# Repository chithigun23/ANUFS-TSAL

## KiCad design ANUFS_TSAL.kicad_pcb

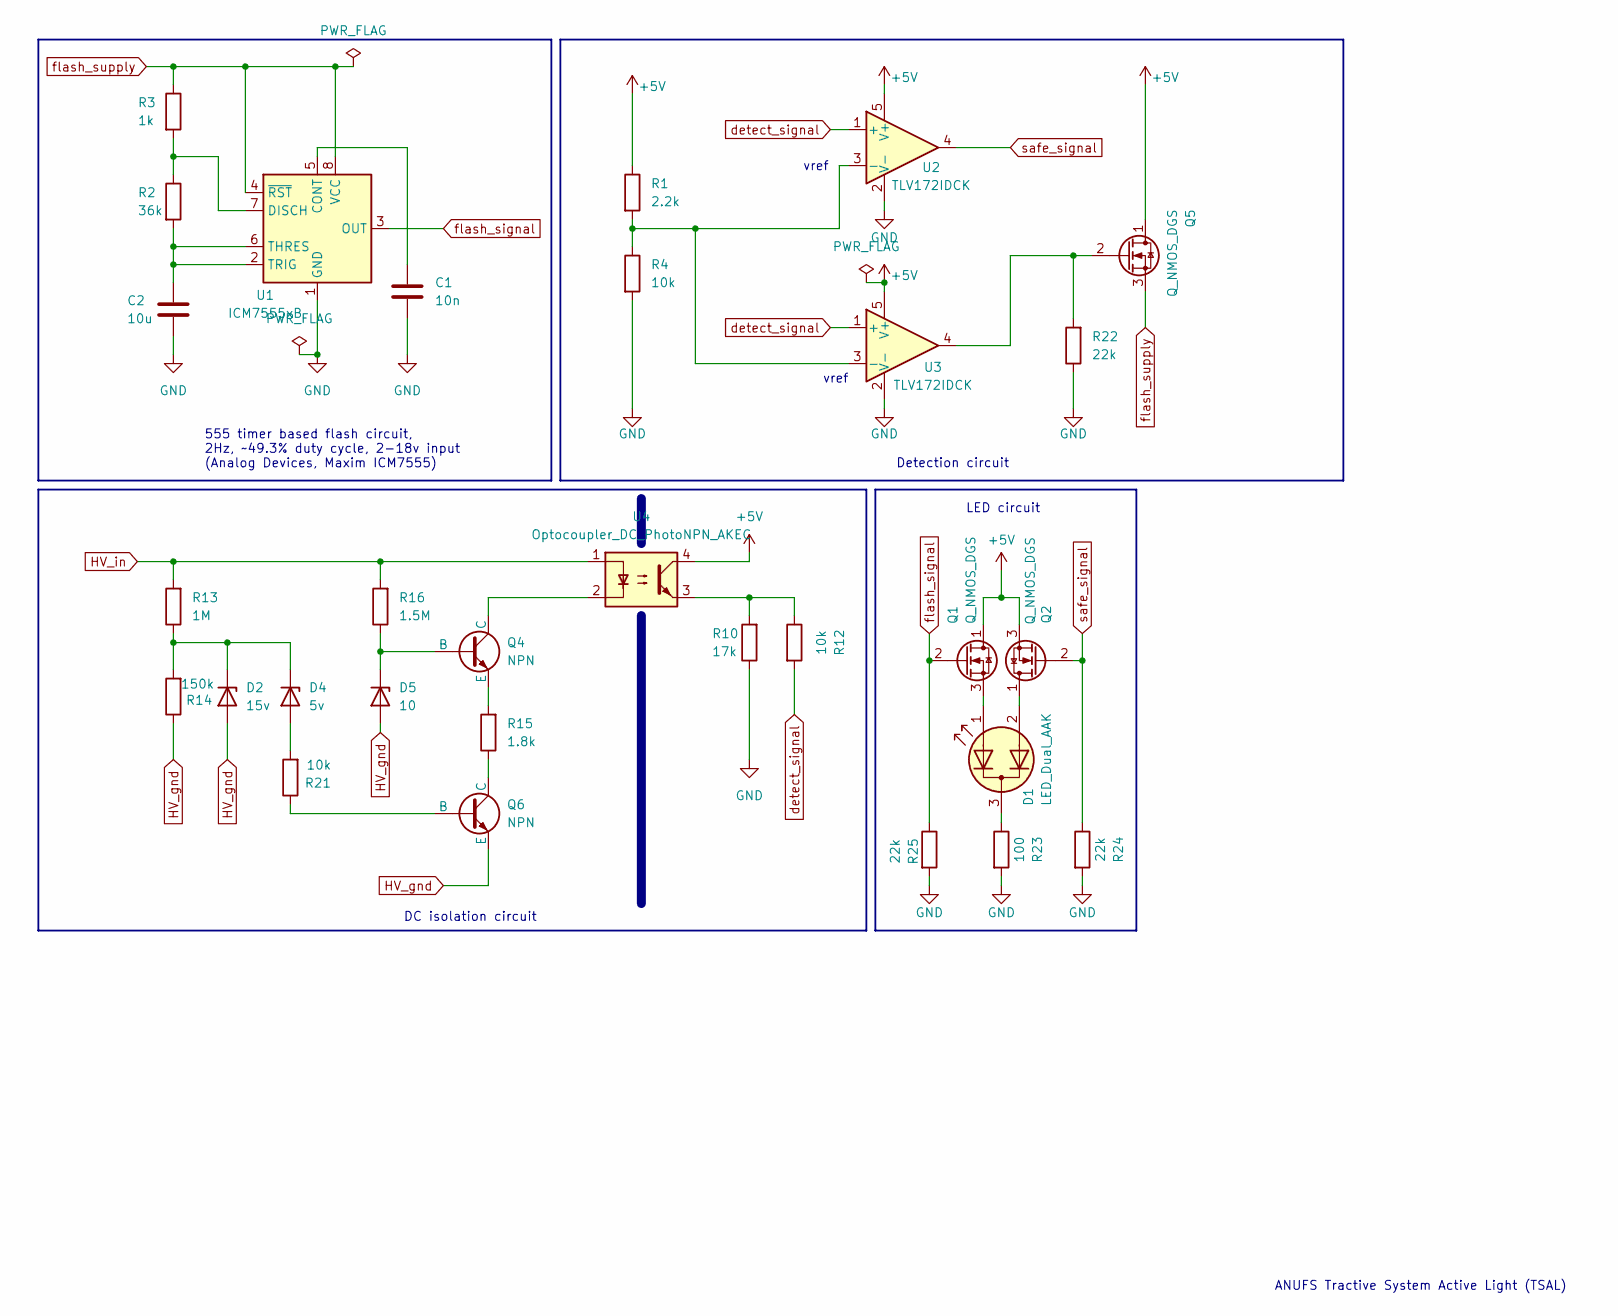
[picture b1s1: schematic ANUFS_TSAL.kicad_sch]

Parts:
C1: 10n; C_0805_2012Metric
C2: 10u; C_Elec_10x10.2
D1: LED_Dual_AAK; LED_D10.0mm-3
D2: 15v; D_SOD-323_HandSoldering
D4: 5v; D_SOD-323_HandSoldering
D5: 10; D_SOD-323_HandSoldering
Q1, Q2, Q5: Q_NMOS_DGS; TSOT-23
Q4: NPN; TO-252-3_TabPin2
Q6: NPN; SOT-23
R1: 2.2k; R_0805_2012Metric
R2: 36k; R_0805_2012Metric
R3: 1k; R_0805_2012Metric
R4, R12, R21: 10k; R_0805_2012Metric
R10: 17k; R_0805_2012Metric
R13: 1M; R_0805_2012Metric
R14: 150k; R_0805_2012Metric
R15: 1.8k; R_0805_2012Metric
R16: 1.5M; R_0805_2012Metric
R22, R24, R25: 22k; R_0805_2012Metric
R23: 100; R_0805_2012Metric
U1: ICM7555xB; SOIC-8_3.9x4.9mm_P1.27mm
U2, U3: TLV172IDCK; SOT-353_SC-70-5
U4: Optocoupler_DC_PhotoNPN_AKEC; Everlight_ITR1201SR10AR

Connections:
+5V: Q1.1 (D), Q2.3 (S), Q5.1 (D), R1.1, U2.5 (V+), U3.5 (V+), U4.4
GND: C1.2, C2.2, R4.2, R10.1, R22.1, R23.2, R24.2, R25.2, U1.1 (GND), U2.2 (V-), U3.2 (V-)
HV_gnd: D2.2 (A), D5.2 (A), Q6.3 (E), R14.1
HV_in: R13.2, R16.2, U4.1
unnamed: D1.1 (A1), Q1.3 (S)
unnamed: D1.2 (A2), Q2.1 (D)
unnamed: D1.3 (K), R23.1
unnamed: D2.1 (K), D4.1 (K), R13.1, R14.2
unnamed: D4.2 (A), R21.2
unnamed: D5.1 (K), Q4.2 (B), R16.1
unnamed: Q4.1 (C), U4.2
unnamed: Q4.3 (E), R15.2
unnamed: Q5.2 (G), R22.2, U3.4
unnamed: Q6.2 (B), R21.1
unnamed: Q6.1 (C), R15.1
unnamed: R10.2, R12.1, U4.3
unnamed: C1.1, U1.5 (CONT)
unnamed: R2.1, R3.2, U1.7 (DISCH)
unnamed: C2.1, R2.2, U1.2 (TRIG), U1.6 (THRES)
unnamed: R1.2, R4.1, U2.3 (-), U3.3 (-)
detect_signal: R12.2, U2.1 (+), U3.1 (+)
flash_signal: Q1.2 (G), R25.1, U1.3 (OUT)
flash_supply: Q5.3 (S), R3.1, U1.4 (~RST), U1.8 (VCC)
safe_signal: Q2.2 (G), R24.1, U2.4

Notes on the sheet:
Detection circuit
vref
ANUFS Tractive System Active Light (TSAL)
555 timer based flash circuit, 2Hz, ~49.3% duty cycle, 2-18v input (Analog Devices, Maxim ICM7555)
DC isolation circuit
LED circuit

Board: 2 copper layers, 30 parts (0 on the bottom side), 24 nets, no tracks yet.
